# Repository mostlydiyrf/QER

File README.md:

# QER
Documents and Kicad (ver.6) design files.

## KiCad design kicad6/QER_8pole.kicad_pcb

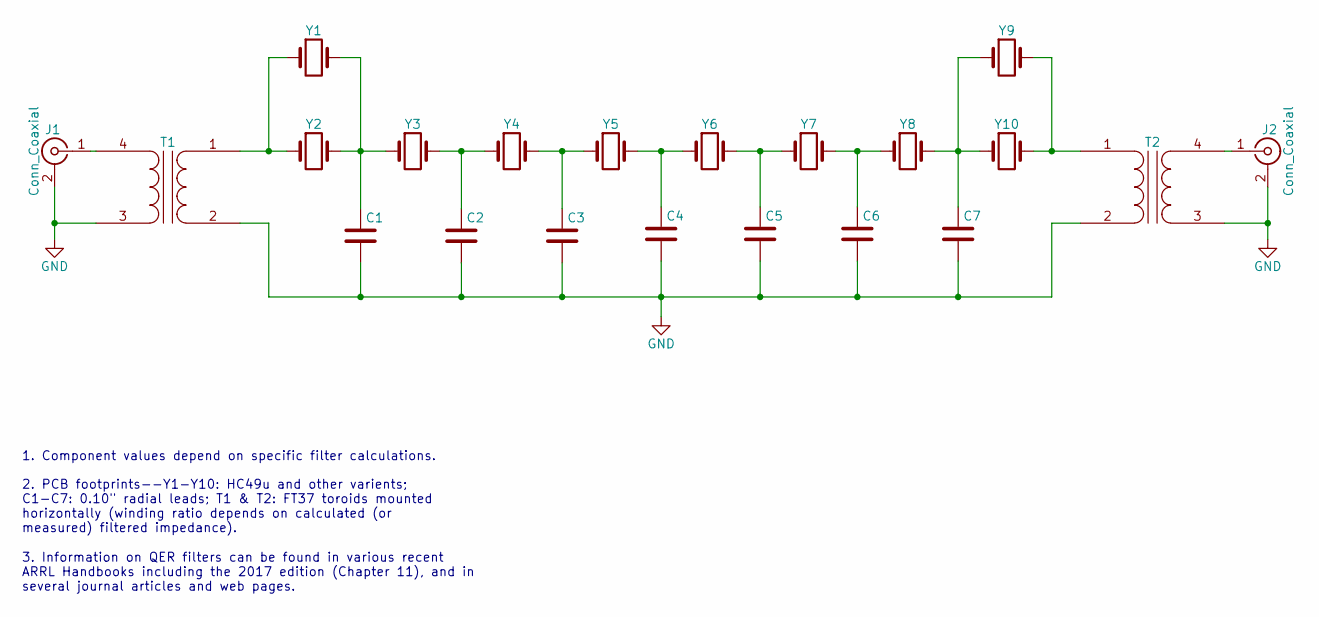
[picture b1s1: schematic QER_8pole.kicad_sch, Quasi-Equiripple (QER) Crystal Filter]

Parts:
C1, C2, C3, C4, C5, C6, C7: C; SR151A200JAR
J1, J2: Conn_Coaxial; SMA_Samtec_SMA-J-P-X-ST-EM1_EdgeMount
T1, T2: Transformer_1P_1S; K7TFC_Impedance_Transformer_T37_Horiz
Y1, Y2, Y3, Y4, Y5, Y6, Y7, Y8, Y9, Y10: Crystal; Crystal_HC49-U_Vertical

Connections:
GND: C1.2, C2.2, C3.2, C4.2, C5.2, C6.2, C7.2, J1.2 (Ext), J2.2 (Ext), T1.2 (AB), T1.3 (SA), T2.2 (AB), T2.3 (SA)
unnamed: C1.1, Y1.2, Y2.2, Y3.1
unnamed: C2.1, Y3.2, Y4.1
unnamed: C3.1, Y4.2, Y5.1
unnamed: C4.1, Y5.2, Y6.1
unnamed: C5.1, Y6.2, Y7.1
unnamed: C6.1, Y7.2, Y8.1
unnamed: C7.1, Y8.2, Y9.1, Y10.1
unnamed: J1.1 (In), T1.4 (SB)
unnamed: J2.1 (In), T2.4 (SB)
unnamed: T1.1 (AA), Y1.1, Y2.1
unnamed: T2.1 (AA), Y9.2, Y10.2

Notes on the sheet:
3. Information on QER filters can be found in various recent ARRL Handbooks including the 2017 edition (Chapter 11), and in several journal articles and web pages.
2. PCB footprints--Y1-Y10: HC49u and other varients; C1-C7: 0.10" radial leads; T1 & T2: FT37 toroids mounted horizontally (winding ratio depends on calculated (or measured) filtered impedance).
1. Component values depend on specific filter calculations.

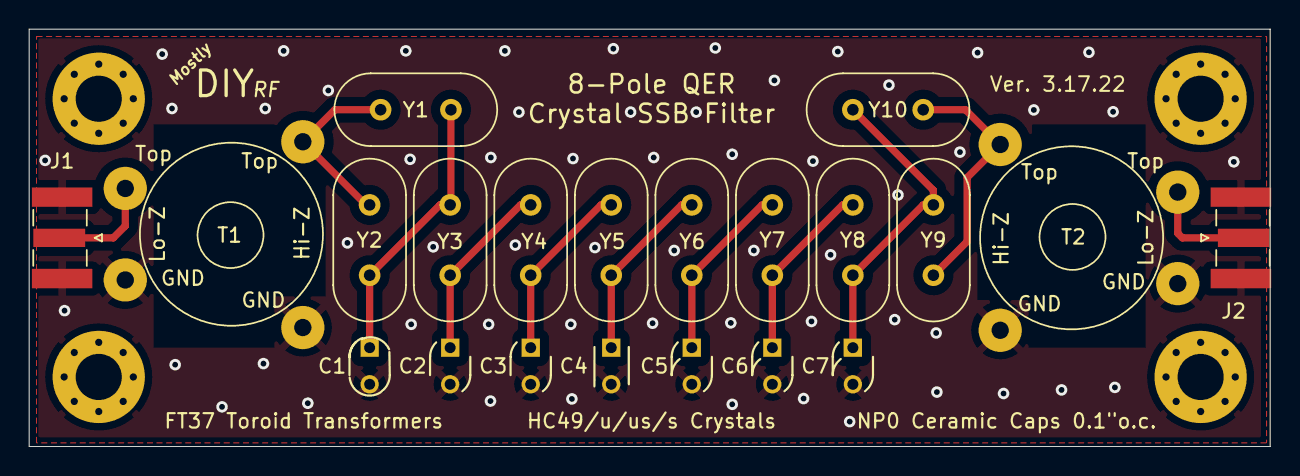
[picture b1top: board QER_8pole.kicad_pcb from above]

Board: 2 copper layers, 86.1 x 29.0 mm, 21 parts (0 on the bottom side), 12 nets.

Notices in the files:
parts and their libraries:
Copyright 2016 Accelerated Designs. All rights reserved.
